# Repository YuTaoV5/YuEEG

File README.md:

# YuEEG · 八通道湿电极 EEG 工程

**新电脑 / 新 agent 从这里接手：[2026-11-01 交接文档](docs/HANDOVER_2026-11-01.md)。最新屏幕已选 AM200Q460460LK；改版尚未完成，下面已通过的 FPC 检查仅属于旧 AM178 附件。**

正在开发 **Rev H：NP-BX1 单节电池、独立模拟／数字板叠放、SCH16T-K01 IMU**，见 [Rev H 状态](hardware/YuEEG_8CH_RevH_Stack/README.md)。主三板与无源屏幕延长板已布线并通过静态检查；探针固定、公差、屏幕最终装配及实物采集仍待验证。当前 `Firmware/ads1299_driver/` 实现连续相对姿态和静止对准后的3秒相对轨迹，用户已选择不部署基站；[使用说明](docs/REVH_INDOOR_NAV.md)包含有效性与漂移边界。开发固件已编译并通过软件测试，尚未实物验证。Rev G 固件和二进制保存在其[冻结目录](hardware/YuEEG_8CH_RevG/firmware/)，以下 Rev G 内容仍是此前已发布的工程评审版本。

以下为**此前发布的 Rev G 工程评审记录**：ADS1299 + ESP32-S3-WROOM-1-N16R8，主板 **70 × 80 mm**、隔离充电副板 **44 × 48 mm**，另有 35 × 67 mm 屏幕载板，各板元件均在正面，AMOLED 在主板上方叠装。

支持隔离 USB CDC 与 Wi-Fi UDP 并行、microSD 原始帧备份、状态灯和 CO5300 AMOLED。主板仅由受保护的 2S 电池供电采集，副板提供独立充电 Type-C。**充电前拔下整个电极线束。**

- [使用指南](docs/GETTING_STARTED.md) · [硬件入口](hardware/README.md)
- [Rev G 固件、命令和协议](hardware/YuEEG_8CH_RevG/firmware/ads1299_driver/README.md) · [Rev H 开发固件](Firmware/ads1299_driver/README.md)
- [Rev G 设计与复核](hardware/YuEEG_8CH_RevG/DISPLAY_INTEGRATION.md)
- [完整评审包](hardware/YuEEG_8CH_RevG_AM178_review.zip)
- [目录说明](docs/PROJECT_STRUCTURE.md) · [更新记录](CHANGELOG.md)

| 项目 | Rev G 历史设计 |
|---|---|
| 采集 | ADS1299，8 通道湿电极，默认 500 SPS、增益 12，共享 REF、独立 BIAS |
| 控制器 | ESP32-S3-WROOM-1-N16R8，双核 240 MHz、16 MB Flash、8 MB PSRAM |
| 电源 | 模拟 ±2.5 V；2S 电池保护/均衡在主板，隔离充电在副板 |
| Type-C | 主板 DATA/FLASH 隔离数据；副板 CHARGE 无数据，不给采集电路供电 |
| 显示 | OSPTEK AM178Q368448LK CO5300 QSPI，10 mm 绝缘支柱 + 35 × 67 mm 两层载板 |
| 存储 | SDMMC 1-bit microSD，128 KiB 缓冲，50 字节带 CRC 原始帧 |
| 装配 | 普通 PTS645 SMT 按键、电解电容在正面；三块板背面无贴片器件 |
| PCB | 主板 305 封装 / 16 页；副板 50 封装 / 4 页，均为四层；新增屏幕载板 15 封装 / 1 页、两层 |

屏幕图案为示意。PCB 面积不等于整机体积，电池和外壳尚未选定。20 芯直通有键屏幕线束、通孔装配和焊盘内过孔填孔封帽要求见交付包。主板与载板静态 ERC/DRC/未连接/原理图一致性均为零，隔离副板沿用 Rev F 零错误报告，固件已编译且 6 项主机协议测试通过；实物噪声、并发、充电、温升和隔离验证尚未完成，不能视为已获人体使用放行。

```powershell
python Firmware/tools/test_protocol.py
python scripts/verify_review.py
```

Rev D、Rev E、Rev F 保持冻结，可从 [历史索引](hardware/archive/README.md) 回溯。项目许可为仓库中的 [MIT License with Restrictions](LICENSE)，不是不附加限制的标准 MIT。

2026-11-01：Rev H 模拟／数字板的层间接口已改为专用贴片 BTB（0.8mm、20触点、8.5mm合高），撤销排针／排母方案；原生检查已通过，具体淘宝配对SKU仍待确认。详见[贴片板间连接说明](docs/REVH_SMT_BTB.md)。

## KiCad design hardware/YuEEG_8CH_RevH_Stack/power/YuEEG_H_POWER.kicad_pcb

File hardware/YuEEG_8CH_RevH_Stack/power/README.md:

电源板改为 Sony NP-FW50 两线电池输入、保护和供电管理。这里的 BOM_source.csv 与 review/expected_source.json 是旧 Rev G 来源记录，含已弃用充电/均衡器件，不可用于制造。新原理图为 YuEEG_H_POWER.kicad_sch，采用 TPS26600 保护链，PCB 34×18 mm，仅几何试排、无走线；JP1 电池触点暂用排针占位，必须实物选型替换。详见 ../../../docs/REVH_CIRCUIT_PROGRESS.md，不能用于制造。

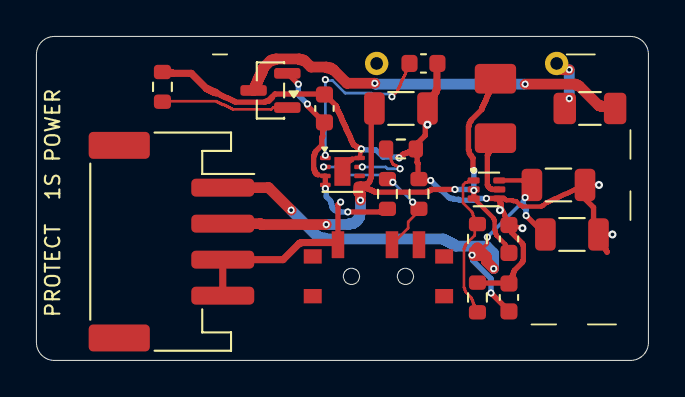
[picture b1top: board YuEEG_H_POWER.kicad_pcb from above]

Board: 2 copper layers, 34.0 x 18.0 mm, 21 parts (1 on the bottom side), 12 nets.

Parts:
CP1: 1u 10V X7R; C_0603_1608Metric
CP2, CP5, CP6: 22u 25V X5R / C3216X5R1E226M160AB; C_1206_3216Metric
CP3: 10n 16V X7R; C_0603_1608Metric
CP4, CP7: 100n 16V X7R; C_0603_1608Metric
FP1: 2A / Littelfuse 0466002.NRHF / 63V fast; Fuse_1206_3216Metric
JP1: 2x Mill-Max 0906-1-15-20-75-14-11-0 / D+ B-; NPBX1_MillMax0906_Dplus_Bminus_10mm
JP2: 1=5V 2=CELL_SENSE 3/4=GND; JST_PH_S4B-PH-SM4-TB_1x04-1MP_P2.00mm_Horizontal
LP1: 1uH / TDK SPM4015T-1R0M-LR; TDK_SPM4015_LR
QP1: DMP2035U-7; SOT-23
RP1: 196k 0.1%; R_0603_1608Metric
RP2, RP6: 100k 0.1%; R_0603_1608Metric
RP3: 1.37k 1% / 1.50A nominal; R_0603_1608Metric
RP4: 100k 1%; R_0603_1608Metric
RP5: 732k 0.1%; R_0603_1608Metric
SWP1: OFF:1-2 / RUN:2-3; SW_SPDT_PCM12
UP1: TPS259530DSGR / latch fault; Texas_DSG0008A_WSON-8-1EP_2x2mm_P0.5mm_EP0.9x1.6mm
UP2: TPS61023DRLR / 5V boost; SOT-563

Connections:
BAT_PROTECTED_SENSE: CP2.1, CP4.1, JP2.2, LP1.1, UP1.5, UP2.2, UP2.3
GND: CP1.2, CP2.2, CP3.2, CP4.2, CP5.2, CP6.2, CP7.2, JP1.2, JP2.3, JP2.4, RP2.2, RP3.2, RP4.2, RP6.2, SWP1.1, UP1.8, UP1.9, UP2.4
PACK_FUSED: FP1.2, QP1.3
PACK_POS: FP1.1, JP1.1
PACK_RP: CP1.1, QP1.2, RP1.1, UP1.3, UP1.4
P_DVDT: CP3.1, UP1.1
P_FB: RP5.2, RP6.1, UP2.1
P_GATE: QP1.1, RP4.1
P_ILM: RP3.1, UP1.7
P_SW: LP1.2, UP2.5
P_UV: RP1.2, RP2.1, SWP1.2, UP1.2
SYS_5V: CP5.1, CP6.1, CP7.1, JP2.1, RP5.1, UP2.6

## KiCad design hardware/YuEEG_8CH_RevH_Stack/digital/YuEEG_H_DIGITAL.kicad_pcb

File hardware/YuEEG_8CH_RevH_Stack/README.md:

# YuEEG Rev H 三板叠装 — 开发中

**交接更新：用户已选择 AM200Q460460LK 2英寸屏幕。详见[交接文档](../../docs/HANDOVER_2026-11-01.md)和[新屏草稿](display_am200/README.md)。新屏针序转换及固件尚未完成；下文 AM178 与 display_link 的通过结果属于旧屏基线，不是新屏放行。**

最新电池为 **Sony NP-BX1（单节）**，覆盖 NP-FW50／2S 版本。电池与最上层屏幕／数字板／模拟板叠层体并排；拆下电池使用专用充电器。详情见 [NP-BX1 电源改版](../../docs/REVH_NPBX1_POWER.md)。

模拟／数字板均为 48×60 mm，电源条板 34×18 mm。三板共 **285 个电气位号、286 个装配器件**（135／129／22；电源板 JP1 为两根探针组成的一个位号），最新 ERC、DRC、未连接、原理图一致性问题均为零，文件哈希及检查时间见 `review/current_check_summary.json`。侧键位于左侧板边，具有 ALPS 安装面禁铜区。数字板新增 SCH16T-K01 和独立LDO，新增16个器件使用叠层间隙，背面SMT原为25个，换用贴片板间公座后为26个；除JH1外，其余原有112个及全部16个IMU器件位置保持。

用户已明确选择 **USB 隔离继续放数字板，接受叠层板超出屏幕**。Type-C／ADuM4160／主机侧保护保留原位；电源条板保持电池保护与升压功能及原 PH4 电源／电压检测线束。USB 迁移到条板的试排与电气草稿已停止归档，不是本版电路。

模拟／数字板已有三处上下同轴的 2.4 mm M2 绝缘固定内切口，位于 Edge.Cuts，不能在 CAM 中丢弃。数字板电感已选定 TDK SPM4015T-2R2M-LR。Rev H 开发固件增加 NP-BX1 带载电压遥测，编译与六项协议测试通过；源文件与开发二进制在 `firmware/`，并非实物验证或生产放行。

短线束 JP2→JH2：1=SYS_5V，2=BAT_PROTECTED_SENSE，3/4=GND。针 2 用于升压前电芯电压检测，不再与针 1 并联。板间 JH1 的 1／19 针仍是并联 SYS_5V。

**尚未完成制造放行**：JP1 已安装双探针封装并完成布线；电池座底座、条板压条与可调后挡块已有实体 STEP／STL，名义装拆、防呆、紧固件与线束筛查通过，详见[电池座机械样件](../../docs/REVH_BATTERY_CRADLE.md)。实际 Sony 电池、探针压缩、公差、材料及受力仍须验收；屏幕 FPC 插接高度、最终支撑件和整机三维隔离未验证。旧 `mechanical/` 屏下电池方案已失效。静态检查不代表采集性能、装配或人体连接安全已经验证。

`archive/` 保留已失效的 2S 电源板及接口迁移前源文件，只供追溯。`BOM_source.csv`、`expected_source.json` 是旧版来源，不能作为生产依据。当前器件清单与连接表为各板 `BOM.csv`、`review/expected_connections.json`。本目录尚未发布制造包；不要使用旧 Rev G Gerber 代替本版。

`fabrication_engineering/` 是带源 PCB 哈希的 Gerber／钻孔／SMT 坐标工程复核导出，**不可直接下单**；电池探针与屏幕连接定型后必须重新生成。机械复核见 [记录](../../docs/REVH_MECHANICAL_REVIEW.md)。

新增[屏幕短 FPC 延长板工程样板](display_link/README.md)，用于保持屏幕最上层而保留现有数字板母座。用户已确认配对公母头可在淘宝购买；附件原理图和布线检查已通过，折弯区无过孔及斜向走线。实际针序、加工叠层及屏幕背面装配尚待确认，不能据此视为屏幕机械定型。

现已找到鱼鹰官方淘宝1.78寸屏幕商品及“单屏／连接器”两个具体SKU，官方GitHub资料也已按固定提交重新核对。第4／5页机械图没有新增折回Z尺寸，第6页VDDIO范围变化单独记录，当前1.8V设计继续保留。商品带触摸，当前板仅使用显示，触摸数据脚闲置；实际屏幕和配套连接器料号仍须确认，见[采购与资料复核](../../docs/REVH_AM178_MECHANICAL_REVIEW.md)。

屏幕附件已修正两个固定焊盘到斜边间距不足的问题，增加0.30mm铜边距及0.15mm外露焊盘间距规则，补强区域与材料目标也已明确在原生文件中。新轮廓、折弯与线束已复核，见[FPC加工几何说明](../../docs/REVH_FPC_FAB_REVIEW.md)；该附件仍待实际配对、屏背尺寸和工厂叠层确认。

数字板 JH2 已改为**朝右出线的 S4B-PH-K-S 卧式通孔 PH4**，减少向屏幕 FPC 弯折区出线的风险。已同步电路、布线、BOM 与工程导出；该通孔接口焊后需将背面焊尾／焊锡总突出量控制在 1.2 mm 以内。具体线束路径与叠层条件见[电源线束装配说明](../../docs/REVH_POWER_HARNESS.md)，实际线束和完整装配仍未验证。

模拟电源区已前移 C405 并增加本地接地过孔，全层禁铜区扩展到 Y=47.5…60 mm；USB 嘴部增加上下同形的 0.8 mm 深圆角避让。对应 HRO 接口已有本地原始尺寸包络，PH4 模型的 Y 方向已纠正。检查范围及装配假设见[叠层复核改版](../../docs/REVH_STACK_REFINEMENT.md)。

屏幕延长板邻近的 R1101 已指定 YAGEO RC0402FR-0722RL，最大本体高度 0.40 mm；原理图、PCB、BOM 和模型已同步，局部筛查另预留 0.10 mm 焊接抬高。替代料必须复核装配高度。完整目标的已实现项与缺项见[完成条件审查](../../docs/REVH_COMPLETION_AUDIT.md)。

双探针改版已集成：JP1.1=D+、JP1.2=B−、10mm 间距，Mill-Max 0906 双针在 B 面，电源条板为 1.0mm。BOM 的 JP1 数量为2，其余SMT仍在F面。见[装配要求](../../docs/REVH_POGO_INTEGRATION.md)。用户已明确授权上传模型派生尺寸、图示、散列和据此修改的PCB／文档，原始STEP／JPG不发布；决定记录为 `review/publication_authorization.json`。

新增 [SCH16T 设计与验证范围](../../docs/REVH_IMU_DESIGN.md)。IMU稳压器／输入电容与AFE C220有投影重叠，要求局部实测板面净距≥8.3mm并按装配高度限制验收。当前开发固件实现连续DRDY采样、相对姿态及静止对准后的3秒相对轨迹，USB／UDP9002输出和SD `.yim` 备份。用户已选择不部署基站，航向没有北向参考，轨迹到期／异常置无效；见[相对运动说明](../../docs/REVH_INDOOR_NAV.md)。编译、6项EEG协议测试、10项运动协议测试及36项实际C++核心检查通过，尚未实物验证。

已按厂家Rev6建议在IMU本体下方加入随封装移动的六层铺铜避让，并用明确地线恢复连接；庭院扩大为14.7×13.4mm。新增地过孔通过对SMT焊盘的独立孔距检查。当前EEG SPI2采样已重查：SCLK有参考铜，CS/MOSI/MISO缺铜点位于信号过孔反焊盘邻域；USB参考层检查见对应报告；DRDY／复位／启动和部分显示线路的局部回流仍须实测，不能仅以DRC判定信号质量。

2026-11-01：上下板 JH1 已由排针／排母改为 0.8mm、20触点、8.5mm合高的专用 SMT BTB 公母座，中心(43.7,21)mm。数字板无板间连接器金属焊尾穿到屏幕面。已适配SGDCONN PH0.8/H40公座与H45母座；淘宝SKU及两页图纸已核实。选型、逻辑针号和装配约束见[贴片板间连接说明](../../docs/REVH_SMT_BTB.md)。制造导出仍为工程版。

2026-11-01：电源条板 JP2 已改为侧向出线，坐标(7.5,11.4)、270°；RP4移至(7.0,2.8)，其余19个位号摆放不变。P_SW/P_FB走线几何保持一致。侧通道改为7mm，条板和电池整体下移1.4mm，完整名义线束最高Z从24.95降至15.35mm。见[侧向改版](../../docs/REVH_SIDE_POWER_PORT.md)与[完整路线](../../docs/REVH_COMPLETE_POWER_HARNESS.md)。这些数值不代表实测整机厚度；屏幕、固定件、线材及电池仓仍须核定。

JP1探针成品孔已由0.60增至0.70mm，按尾针最差直径与公开插件孔公差检查焊接间隙；全部位置和电气分配不变。JH1定位孔另需板厂接受0.65+0.03/-0mm，不能套用常规NPTH公差。见[孔径复核](../../docs/REVH_POGO_HOLE_TOLERANCE.md)。

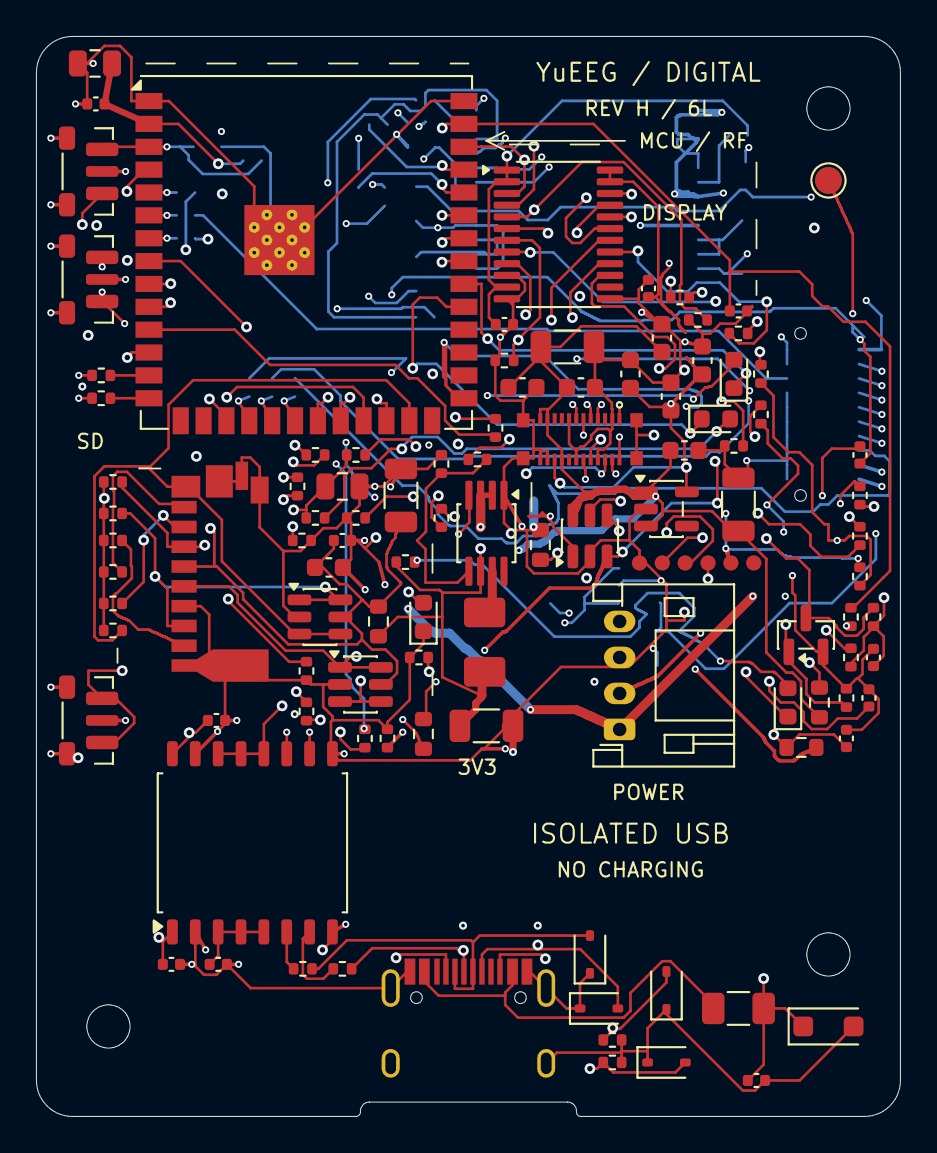
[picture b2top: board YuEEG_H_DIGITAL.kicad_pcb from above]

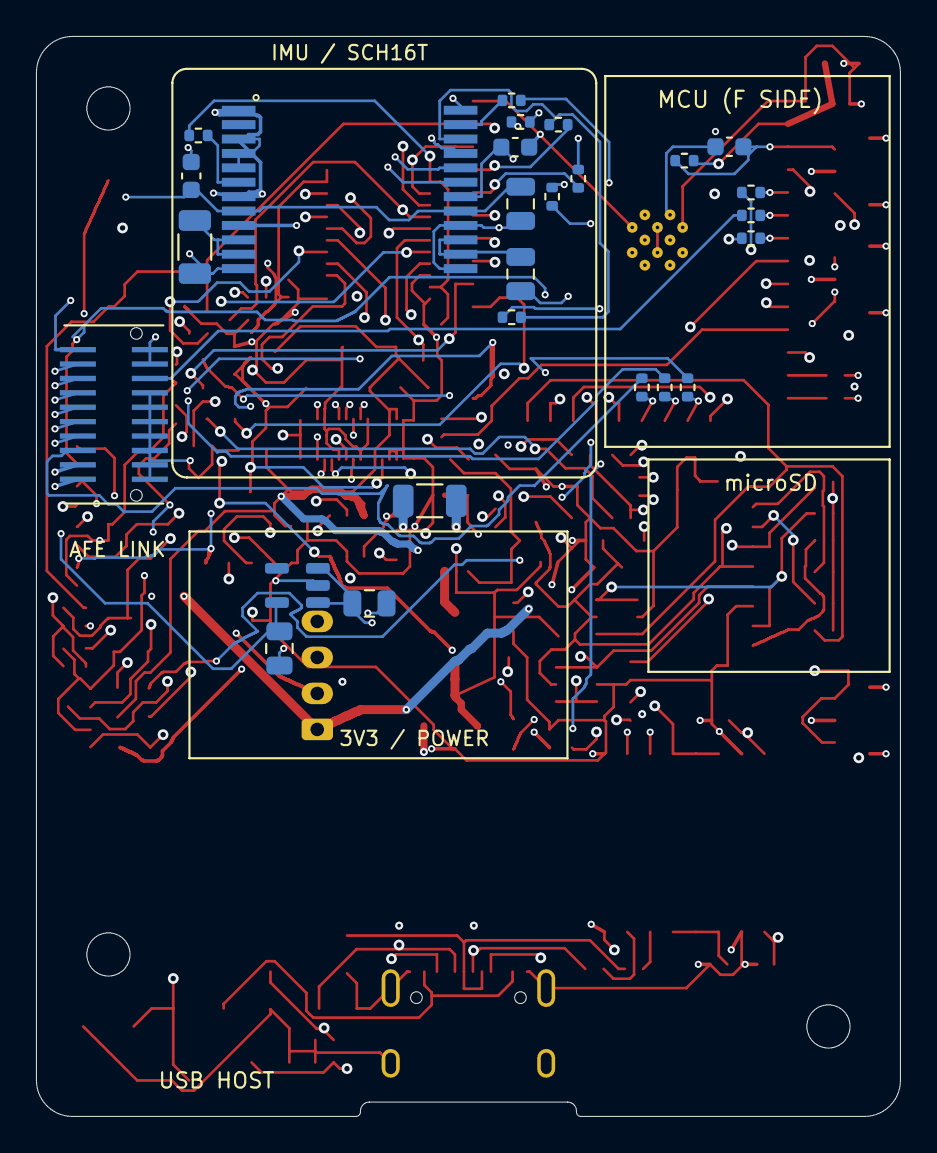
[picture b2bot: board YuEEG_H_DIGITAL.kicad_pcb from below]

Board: 6 copper layers, 48.0 x 60.0 mm, 132 parts (26 on the bottom side), 96 nets.

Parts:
C301, C1006, C1103, C2003: 1u 10V; C_0603_1608Metric
C302, C305, C1003, C1008, C1009, C1012, C1102: 100n 10V; C_0402_1005Metric
C303: 10u 10V; C_0805_2012Metric
C304: 22u 10V; C_0805_2012Metric
C406: 22u 25V X5R / C3216X5R1E226M160AB H1.8max; C_1206_3216Metric
C407, C1002, C1010, C1101: 22u 10V X7R; C_1206_3216Metric
C701, C702, C703, C901: 100n 16V; C_0402_1005Metric
C1001: 1n 25V; C_0402_1005Metric
C1007: 4.7u 10V; C_0603_1608Metric
C1120: 10n 10V; C_0402_1005Metric
C1801, C1803: 1u 50V 5% X7R / eff0.7..1.3u; C_0805_KEMET_Flex_Max2p35x1p55
C1802: 10u 25V X7R / eff4.6..15u; C_1206_3216Metric
C1804, C1805: 100n 50V 5% X7R / eff70..130n; C_0603_1608Metric
C1806, C1807: 4.7u 25V X7R / LDO eff>=1u; C_0805_2012Metric
C2001: 10u 10V X7R; C_0603_1608Metric
C2002, C2004, C2005: 100n 10V; C_0603_1608Metric
D602, D603: PESD5V0U1BAF; D_SOD-323
D604, D605: PESD5V0S1BA; D_SOD-323
D901: SMF5.0A DATA VBUS; D_SOD-123F
D1101, D1102: USBLC6-2SC6; SOT-23-6
F901: 500mA HOLD PTC; Fuse_1206_3216Metric
FB1101: BLM18PG121SN1D / 120R@100MHz; R_0603_1608Metric
H1, H2, H3: M2 NYLON ONLY; MountingHole_M2_Routed_2p4
J301: 3V3 / IMU_CS / IMU_DRDY / EN / BOOT / GND; Debug_Pogo_1x06_P1p27
J601: USB-C DATA / FLASH - ISOLATED; USB_C_Receptacle_HRO_TYPE-C-31-M-12
J1101: KINGCONN 7TFCN-FA-1010-C / H3.75; KINGCONN_7TFCN_FA_1010_C_NotchedShield
J2002: OK-14F024-04 / AM178Q368448LK; OCN_OK_14F024_04
JH1: SGDBM-08-020P-H40 / SMT BTB; SGD_BM08_020_H40_Logical
JH2: S4B-PH-K-S / 5V+CELL SENSE / RIGHT; JST_PH_S4B-PH-K_1x04_P2.00mm_Horizontal
L401: 2.2uH / TDK SPM4015T-2R2M-LR; TDK_SPM4015_LR
LED801: POWER; LED_0603_1608Metric
LED802: RUN; LED_0603_1608Metric
LED803: WIFI; LED_0603_1608Metric
LED804: FAULT; LED_0603_1608Metric
Q1001: MMBT3904 OE ENABLE; SOT-23
R301, R302, R303, R304, R305, R306: 33R; R_0402_1005Metric
R307, R308, R1002, R1111, R1112, R1113, R1114, R1115, R1116, R1120, R1801, R1806: 10k; R_0402_1005Metric
R309: 330k 1%; R_0402_1005Metric
R310: 100k 1%; R_0402_1005Metric
R403: 31.2k 0.1%; R_0402_1005Metric
R404: 10k 0.1%; R_0402_1005Metric
R701, R702, R703, R704: 24R 1%; R_0402_1005Metric
R840, R841, R842, R843: 2.2k; R_0402_1005Metric
R901, R902: 5.1k 1%; R_0402_1005Metric
R1001, R1004: 100k; R_0402_1005Metric
R1003: 1k; R_0402_1005Metric
R1005: 1M; R_0402_1005Metric
R1021, R1022, R1023, R1024, R1025, R1026, R1027, R1802, R1803, R1804, R1805: 22R; R_0402_1005Metric
R1031, R1032, R1033, R1034, R1035, R1036, R1037: 47k; R_0402_1005Metric
R1101: 22R 1% / RC0402FR-0722RL; YAGEO_RC0402FR_0722RL
R1807: 100R; R_0402_1005Metric
R2001: 0R; R_0603_1608Metric
R2002: 100k; R_0603_1608Metric
R2003, R2004: 47k; R_0603_1608Metric
SW301: ALPS SKRTLBE010 / RESET; ALPS_SKRTLBE010_GroundedShell
SW302: ALPS SKRTLBE010 / BOOT; ALPS_SKRTLBE010_GroundedShell
SW1001: ALPS SKRTLBE010 / REC; ALPS_SKRTLBE010_GroundedShell
TP404: +3V3; TestPoint_Pad_D1.5mm
U2: ESP32-S3-WROOM-1U-N16R8; ESP32-S3-WROOM-1U
U402: TPS62160DGKR; MSOP-8_3x3mm_P0.65mm
U701: ADuM4160BRIZ / enhanced creepage; ADuM4160_RI16_8p5gap
U1001: TPS22918DBVR AMOLED POWER; SOT-23-6
U1003: TPS7A2018PDBVR; SOT-23-5
U1004: SN74AXC8T245PWR / 3V3 -> 1V8; TSSOP-24_4.4x7.8mm_P0.65mm
U1801: SCH16T-K01-1; Murata_SCH16T_SOIC24_14p20x9p30_P0p80
U1802: TPS7A2033PDBVR; SOT23_5_IMU_NoBodySilk

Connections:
+3V3: C302.1, C303.1, C304.1, C407.1, C703.1, C1003.1, C1008.1, C1805.1, FB1101.1, JH1.3, L401.2, R307.1, R308.1, R403.1, R840.1, R841.1, R842.1, R843.1, R1002.1, R1031.1, R1120.1, R1801.1, R1806.1, TP404.1, U2.2, U402.6, U701.12, U701.13, U701.14, U701.16, U1001.1, U1004.1, U1004.2, U1004.11, U1801.18
+3V3_IMU: C1803.1, C1804.1, C1807.1, U1801.8, U1801.17, U1802.5
ADS_CS: JH1.9, R301.2
ADS_DRDY: JH1.13, U2.4
ADS_MISO: JH1.11, U2.21
ADS_MOSI: JH1.7, R302.2
ADS_PWDN: JH1.16, R305.2
ADS_RESET: JH1.15, R304.2
ADS_SCLK: JH1.5, R303.2
ADS_START: JH1.17, R306.2
AM_1V8: C1007.1, C1009.1, C1012.1, C2003.1, C2004.1, J2002.15, R2001.1, U1003.5, U1004.23, U1004.24
AM_CLK_A: R1032.2, R1802.1, U2.12, U1004.4
AM_CLK_B: R1022.1, U1004.20
AM_CLK_P: J2002.5, R1022.2
AM_CS_A: R1031.2, U2.38, U1004.3
AM_CS_B: R1021.1, U1004.21
AM_CS_P: J2002.4, R1021.2
AM_CT: C1001.1, U1001.4
AM_D0_A: R1033.2, R1803.1, U2.17, U1004.5
AM_D0_B: R1023.1, U1004.19
AM_D0_P: J2002.7, R1023.2
AM_D1_A: R1034.2, R1804.2, U2.22, U1004.6
AM_D1_B: R1024.1, U1004.18
AM_D1_P: J2002.6, R1024.2
AM_D2_A: R1035.2, U2.8, U1004.7
AM_D2_B: R1025.1, U1004.17
AM_D2_P: J2002.23, R1025.2
AM_D3_A: R1036.2, U2.9, U1004.8
AM_D3_B: R1026.1, U1004.16
AM_D3_P: J2002.22, R1026.2
AM_OE_BASE: Q1001.1, R1004.2, R1005.1
AM_OE_N: Q1001.3, R1002.2, U1004.22
AM_POWER_EN: R1001.1, R1004.1, U2.35, U1001.3
AM_QOD: R1003.2, U1001.5
AM_RAW: C1002.1, C1006.1, C1010.1, C2001.1, C2002.1, C2005.1, J2002.11, J2002.12, J2002.16, R1003.1, R2003.1, R2004.1, U1001.6, U1003.1, U1003.3
AM_RST_A: R1037.2, U2.10, U1004.9
AM_RST_B: R1027.1, U1004.15
AM_RST_P: J2002.1, R1027.2
BAT_PROTECTED_SENSE: JH2.2, R309.1
BAT_SENSE: C305.1, R309.2, R310.1, U2.39
BUCK_FB: R403.2, R404.1, U402.5
BUCK_SW: L401.1, U402.7
DATA_5V: C701.1, C901.1, D901.1, F901.2, U701.1
DATA_RAW: F901.1, J601.A4, J601.A9, J601.B4, J601.B9
ESP_BOOT: J301.5, R308.2, SW302.1, U2.27
ESP_EN: C301.1, J301.4, R307.2, SW301.1, U2.3
GND: C301.2, C302.2, C303.2, C304.2, C305.2, C406.2, C407.2, C703.2, C1001.2, C1002.2, C1003.2, C1006.2, C1007.2, C1008.2, C1009.2, C1010.2, C1012.2, C1101.2, C1102.2, C1103.2, C1120.2, C1801.2, C1802.2, C1803.2, C1804.2, C1805.2, C1806.2, C1807.2, C2001.2, C2002.2, C2003.2, C2004.2, C2005.2, D1101.2, D1102.2, J301.1, J1101.6, J1101.10, J1101.11, J2002.2, J2002.8, J2002.13, J2002.14, J2002.18, J2002.21, J2002.25, J2002.26, J2002.27, J2002.28, JH1.2, JH1.4, JH1.6, JH1.8, JH1.10, JH1.12, JH1.14, JH1.18, JH1.20, JH2.3, JH2.4, LED801.1, Q1001.2, R310.2, R404.2, R1001.2, R1005.2, R1032.1, R1033.1, R1034.1, R1035.1, R1036.1, R1037.1, R2002.2, SW301.2, SW302.2, SW1001.2, U2.1, U2.40, U2.41, U402.1, U402.4, U701.9, U701.15, U1001.2, U1003.2, U1004.10, U1004.12, U1004.13, U1801.1, U1801.3, U1801.4, U1801.5, U1801.7, U1801.9, U1801.12, U1801.13, U1801.16, U1801.24, U1802.2
HOST_GND: C701.2, C702.2, C901.2, D602.1, D603.1, D604.1, D605.1, D901.2, J601.A1, J601.A12, J601.B1, J601.B12, J601.S1, R901.2, R902.2, U701.2, U701.8
IMU_CS_MCU: J301.2, R1805.1, U2.37
IMU_CS_N: R1805.2, R1806.2, U1801.22
IMU_DRDY: R1807.1, U1801.20
IMU_DRDY_MCU: J301.3, R1807.2, U2.36
IMU_MISO: R1804.1, U1801.19
IMU_MOSI: R1803.2, U1801.23
IMU_RESET_N: R1801.2, U1801.6
IMU_SCLK: R1802.2, U1801.21
IMU_VREGA: C1802.1, U1801.10, U1801.11
IMU_VREGD: C1801.1, U1801.14, U1801.15
KEY_REC: C1120.1, R1120.2, SW1001.1, U2.34
LED_FAULT_K: LED804.1, U2.33
LED_RUN_K: LED802.1, U2.31
LED_WIFI_K: LED803.1, U2.32
MCU_CS: R301.1, U2.18
MCU_MOSI: R302.1, U2.19
MCU_PWDN: R305.1, U2.6
MCU_RESET: R304.1, U2.5
MCU_SCLK: R303.1, U2.20
MCU_START: R306.1, U2.7
SD_3V3: C1101.1, C1102.1, C1103.1, D1101.5, D1102.5, FB1101.2, J1101.4, R1111.1, R1112.1, R1113.1, R1114.1, R1115.1, R1116.1
SD_CD: D1102.3, D1102.4, J1101.9, R1116.2, U2.25
SD_CLK_CARD: D1101.1, D1101.6, J1101.5, R1101.2
SD_CLK_HOST: R1101.1, U2.11
SD_CMD: D1101.3, D1101.4, J1101.3, R1111.2, U2.23
SD_D0: D1102.1, D1102.6, J1101.7, R1112.2, U2.24
SD_DAT1: J1101.8, R1113.2
SD_DAT2: J1101.1, R1114.2
SD_DAT3: J1101.2, R1115.2
STATUS_FAULT_A: LED804.2, R843.2
STATUS_POWER_A: LED801.2, R840.2
STATUS_RUN_A: LED802.2, R841.2
STATUS_WIFI_A: LED803.2, R842.2
SYS_5V: C406.1, C1806.1, JH1.1, JH1.19, JH2.1, U402.2, U402.3, U1802.1, U1802.3
TP_SCL_IDLE: J2002.20, R2004.2
TP_SDA_IDLE: J2002.19, R2003.2
USB_CC1: D604.2, J601.A5, R901.1
USB_CC2: D605.2, J601.B5, R902.1
USB_DOWN_DM: R704.1, U701.11
USB_DOWN_DP: R703.1, U701.10
USB_HOST_DM: D603.2, J601.A7, J601.B7, R702.1
USB_HOST_DP: D602.2, J601.A6, J601.B6, R701.1
USB_MCU_DM: R704.2, U2.13
USB_MCU_DP: R703.2, U2.14
USB_UP_DM: R702.2, U701.6
USB_UP_DP: R701.2, U701.7
USB_VDD1: C702.1, U701.3, U701.4, U701.5
VCI_EN: J2002.24, R2001.2, R2002.1

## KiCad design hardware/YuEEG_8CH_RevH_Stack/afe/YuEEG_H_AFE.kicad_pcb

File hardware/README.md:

# 硬件入口

开发中的新版本为 [Rev H 叠放版](YuEEG_8CH_RevH_Stack/README.md)：NP-BX1 外置充电，模拟／数字板统一 48×60 mm，电源条板 34×18 mm。当前导出仅作工程复核，电池探针接口和屏幕 FPC 尚未完成装配定型。下文为此前已发布的 Rev G 版本。

当前为 [Rev G AMOLED 适配版](YuEEG_8CH_RevG/README.md)：70 × 80 mm 四层主板、35 × 67 mm 两层屏幕载板，配未修改的 Rev F 44 × 48 mm 四层隔离充电副板。各板元件均在正面。屏幕 OSPTEK AM178Q368448LK / CO5300 叠装；主板电池供电，充电前拔下整个电极线束。

- [主板工程](YuEEG_8CH_RevG/YuEEG_8CH_RevG.kicad_pro)
- [屏幕载板](YuEEG_8CH_RevG/display_carrier/YuEEG_DISPLAY_G.kicad_pro)
- [隔离充电副板（沿用 Rev F）](YuEEG_8CH_RevG/isolated_power/YuEEG_8CH_RevF_POWER.kicad_pro)
- [接线、采购与首板验证](YuEEG_8CH_RevG/DISPLAY_INTEGRATION.md)
- [完整评审包，含三块板独立 Gerber ZIP](YuEEG_8CH_RevG_AM178_review.zip)
- [冻结 Rev F](YuEEG_8CH_RevF/README.md) · [历史索引](archive/README.md)

主板和载板静态检查通过；屏幕母座方向需首件导通确认，装配、点亮、噪声和隔离仍待实物验收。

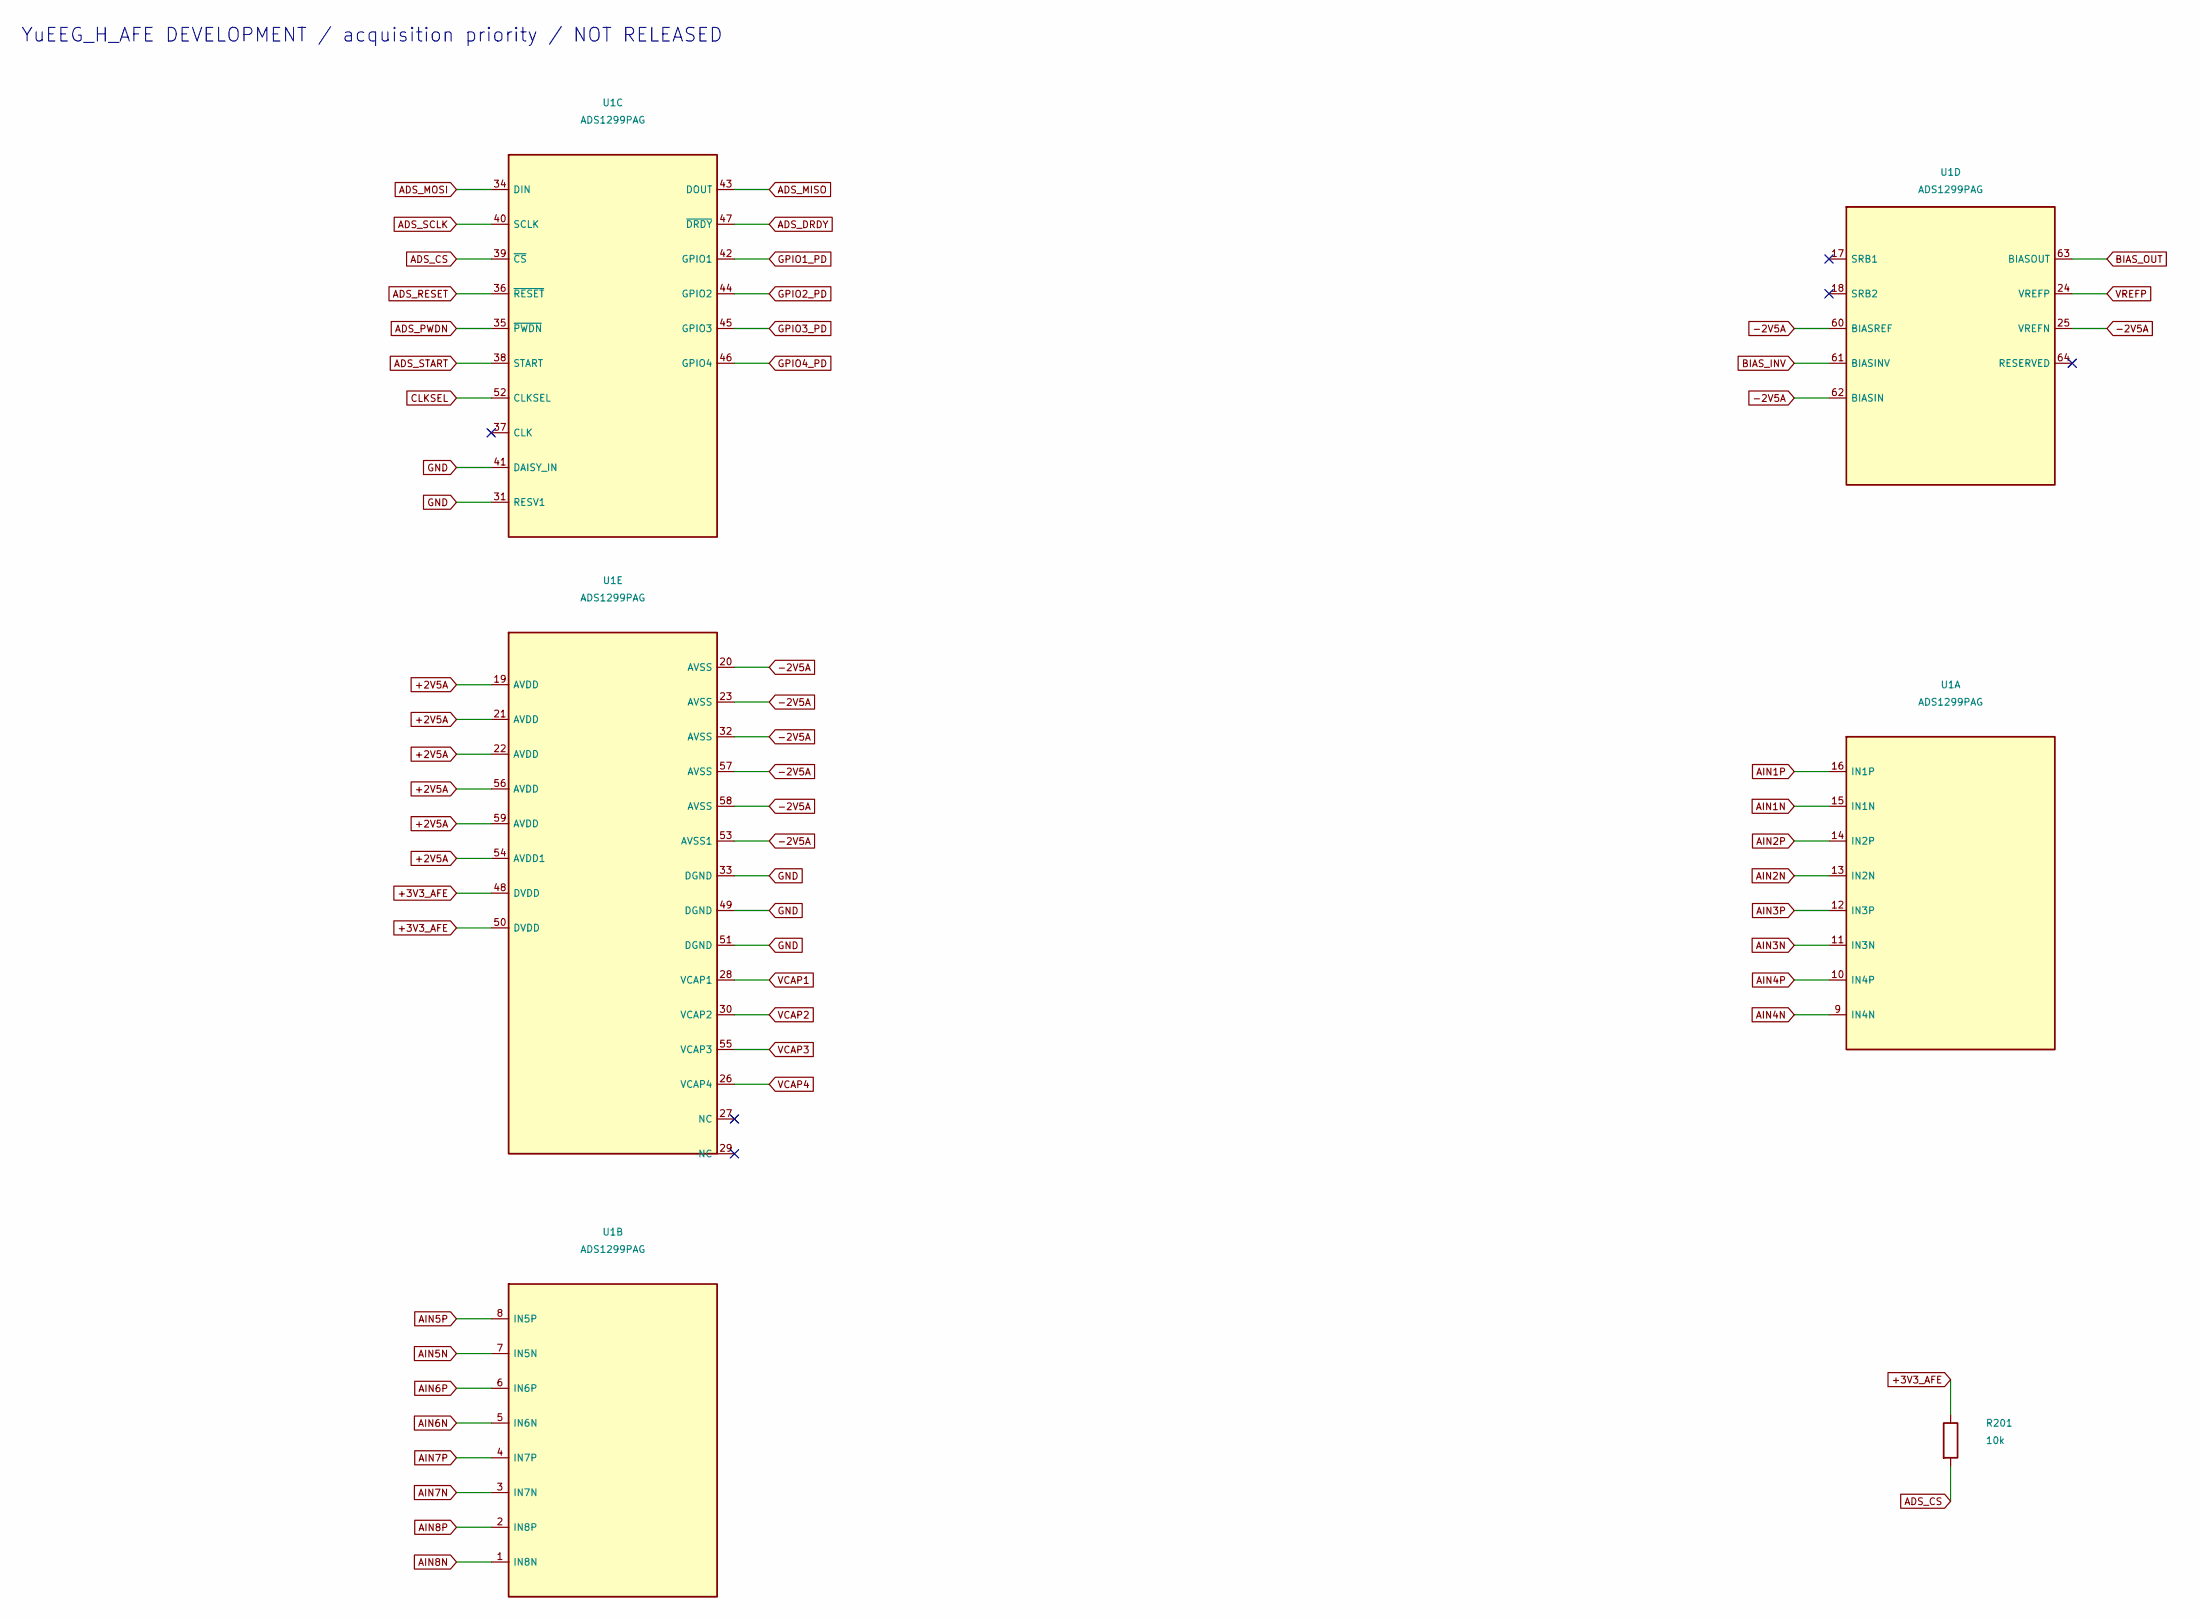
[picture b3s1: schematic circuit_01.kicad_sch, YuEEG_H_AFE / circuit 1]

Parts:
R201: 10k; R_0402_1005Metric
U1: ADS1299PAG; TQFP-64_10x10mm_P0.5mm

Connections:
+2V5A: U1.19 (AVDD), U1.21 (AVDD), U1.22 (AVDD), U1.54 (AVDD1), U1.56 (AVDD), U1.59 (AVDD); also elsewhere on the board
+3V3_AFE: R201.1, U1.48 (DVDD), U1.50 (DVDD); also elsewhere on the board
-2V5A: U1.20 (AVSS), U1.23 (AVSS), U1.25 (VREFN), U1.32 (AVSS), U1.53 (AVSS1), U1.57 (AVSS), U1.58 (AVSS), U1.60 (BIASREF), U1.62 (BIASIN); also elsewhere on the board
ADS_CS: R201.2, U1.39 (~CS); also elsewhere on the board
ADS_DRDY: U1.47 (~DRDY); also elsewhere on the board
ADS_MISO: U1.43 (DOUT); also elsewhere on the board
ADS_MOSI: U1.34 (DIN); also elsewhere on the board
ADS_PWDN: U1.35 (~PWDN); also elsewhere on the board
ADS_RESET: U1.36 (~RESET); also elsewhere on the board
ADS_SCLK: U1.40 (SCLK); also elsewhere on the board
ADS_START: U1.38 (START); also elsewhere on the board
AIN1N: U1.15 (IN1N); also elsewhere on the board
AIN1P: U1.16 (IN1P); also elsewhere on the board
AIN2N: U1.13 (IN2N); also elsewhere on the board
AIN2P: U1.14 (IN2P); also elsewhere on the board
AIN3N: U1.11 (IN3N); also elsewhere on the board
AIN3P: U1.12 (IN3P); also elsewhere on the board
AIN4N: U1.9 (IN4N); also elsewhere on the board
AIN4P: U1.10 (IN4P); also elsewhere on the board
AIN5N: U1.7 (IN5N); also elsewhere on the board
AIN5P: U1.8 (IN5P); also elsewhere on the board
AIN6N: U1.5 (IN6N); also elsewhere on the board
AIN6P: U1.6 (IN6P); also elsewhere on the board
AIN7N: U1.3 (IN7N); also elsewhere on the board
AIN7P: U1.4 (IN7P); also elsewhere on the board
AIN8N: U1.1 (IN8N); also elsewhere on the board
AIN8P: U1.2 (IN8P); also elsewhere on the board
BIAS_INV: U1.61 (BIASINV); also elsewhere on the board
BIAS_OUT: U1.63 (BIASOUT); also elsewhere on the board
CLKSEL: U1.52 (CLKSEL); also elsewhere on the board
GND: U1.31 (RESV1), U1.33 (DGND), U1.41 (DAISY_IN), U1.49 (DGND), U1.51 (DGND); also elsewhere on the board
GPIO1_PD: U1.42 (GPIO1); also elsewhere on the board
GPIO2_PD: U1.44 (GPIO2); also elsewhere on the board
GPIO3_PD: U1.45 (GPIO3); also elsewhere on the board
GPIO4_PD: U1.46 (GPIO4); also elsewhere on the board
VCAP1: U1.28 (VCAP1); also elsewhere on the board
VCAP2: U1.30 (VCAP2); also elsewhere on the board
VCAP3: U1.55 (VCAP3); also elsewhere on the board
VCAP4: U1.26 (VCAP4); also elsewhere on the board
VREFP: U1.24 (VREFP); also elsewhere on the board

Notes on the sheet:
YuEEG_H_AFE DEVELOPMENT / acquisition priority / NOT RELEASED

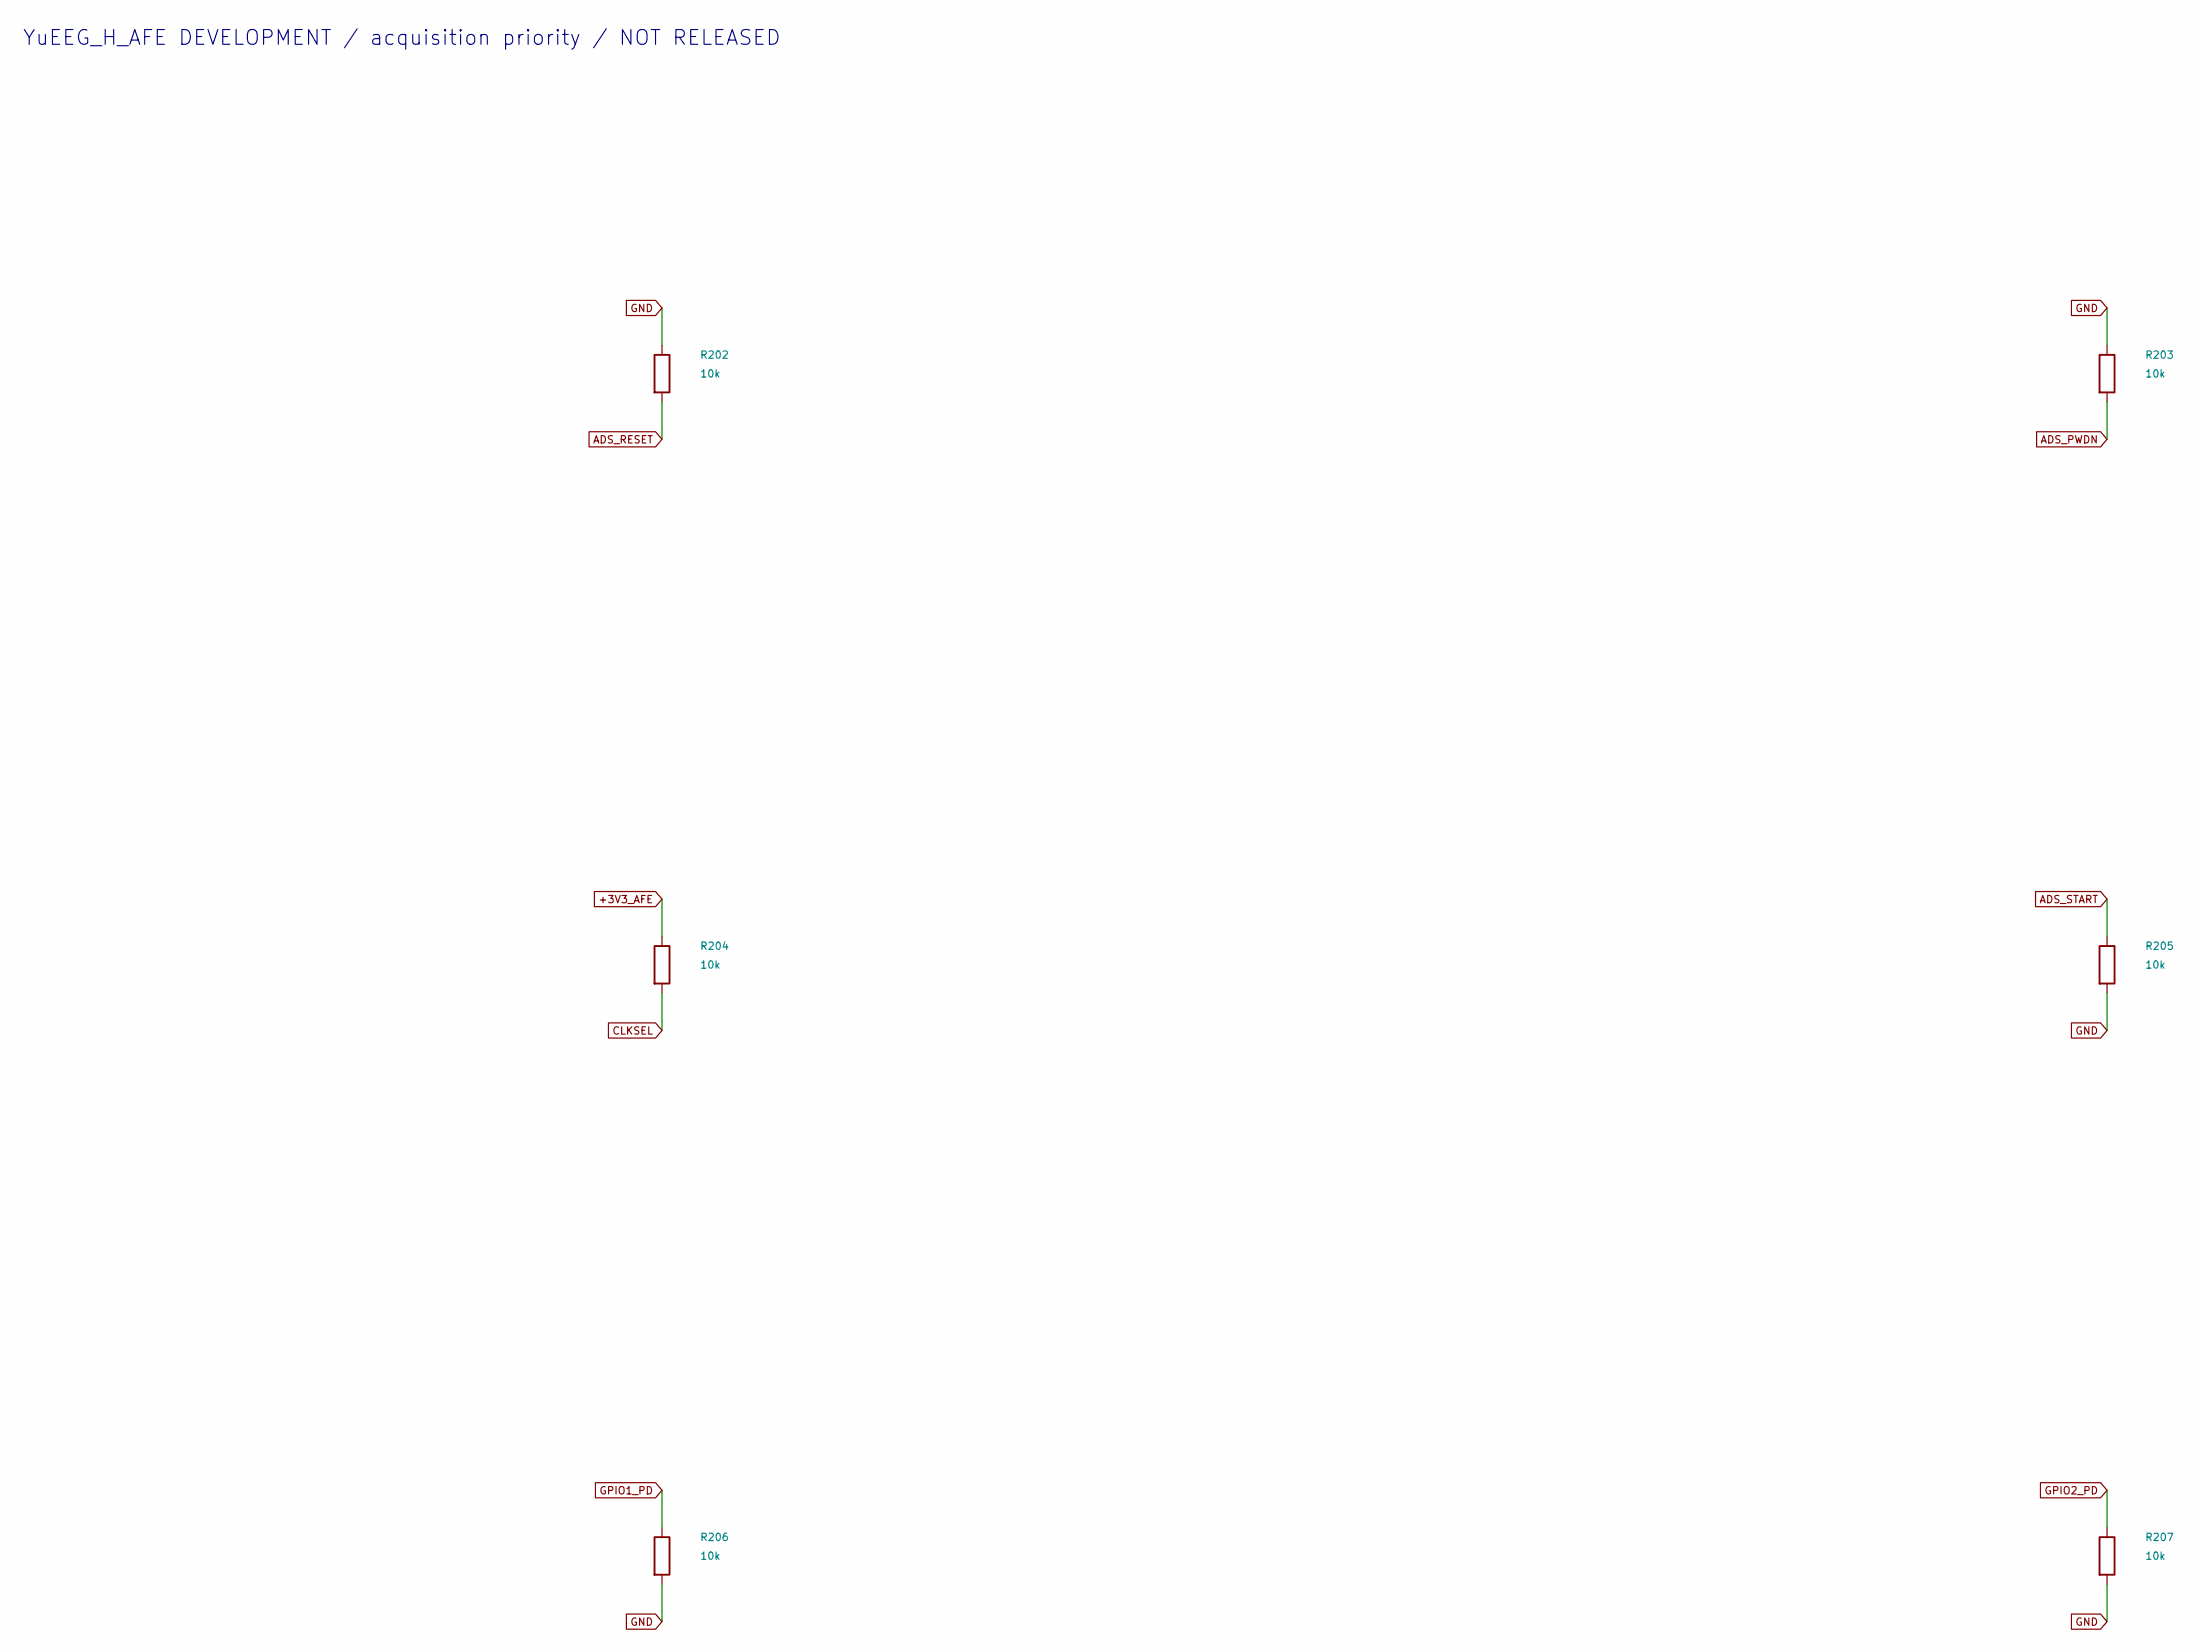
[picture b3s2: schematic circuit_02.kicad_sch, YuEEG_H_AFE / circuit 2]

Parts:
R202, R203, R204, R205, R206, R207: 10k; R_0402_1005Metric

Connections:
+3V3_AFE: R204.1; also elsewhere on the board
ADS_PWDN: R203.2; also elsewhere on the board
ADS_RESET: R202.2; also elsewhere on the board
ADS_START: R205.1; also elsewhere on the board
CLKSEL: R204.2; also elsewhere on the board
GND: R202.1, R203.1, R205.2, R206.2, R207.2; also elsewhere on the board
GPIO1_PD: R206.1; also elsewhere on the board
GPIO2_PD: R207.1; also elsewhere on the board

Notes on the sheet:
YuEEG_H_AFE DEVELOPMENT / acquisition priority / NOT RELEASED
